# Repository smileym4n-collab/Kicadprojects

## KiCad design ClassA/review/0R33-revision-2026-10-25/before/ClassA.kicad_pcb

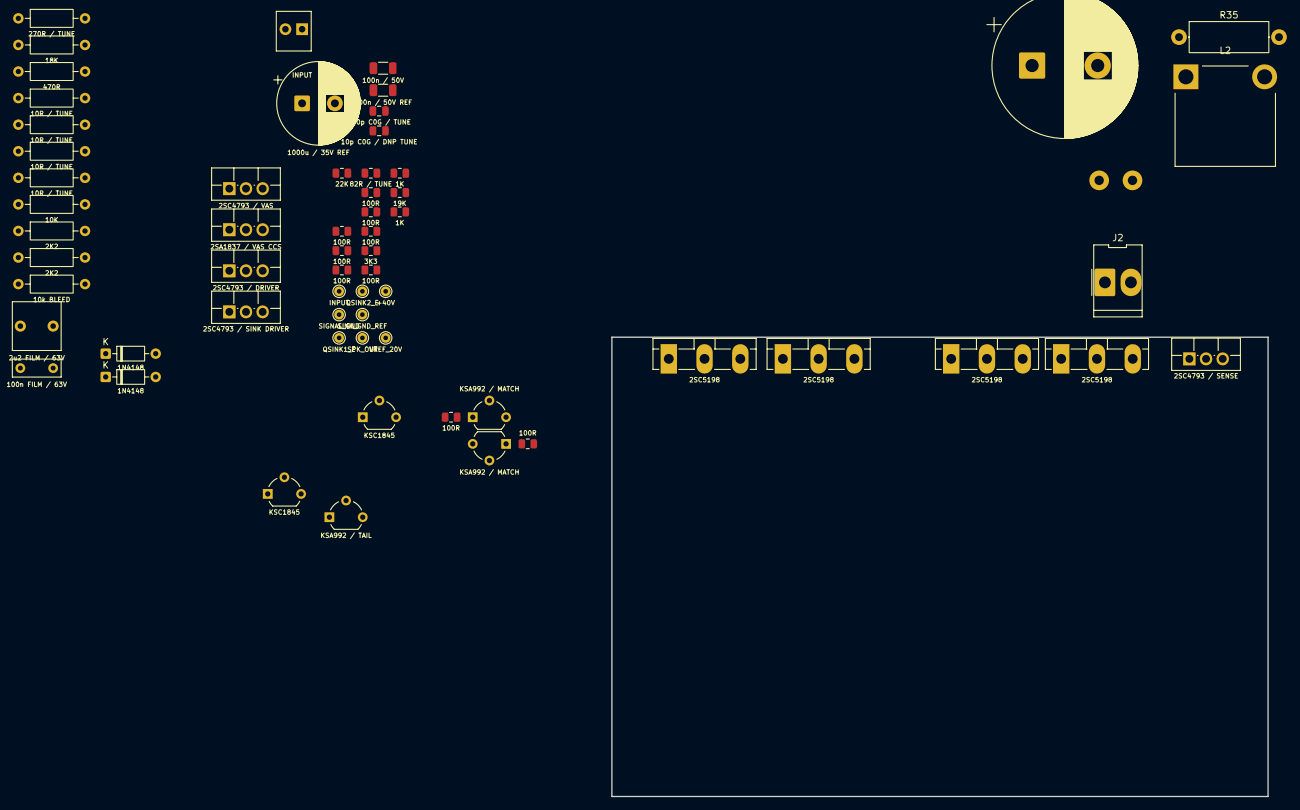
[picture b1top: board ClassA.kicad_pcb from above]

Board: 2 copper layers, 100.0 x 70.0 mm, 63 parts (0 on the bottom side), 35 nets, no tracks yet.

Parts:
C1: 2u2 FILM / 63V; C_Rect_L7.2mm_W7.2mm_P5.00mm
C2: 100p C0G / TUNE; C_0805_2012Metric
C3: 100n FILM / 63V; C_Rect_L7.2mm_W2.5mm_P5.00mm
C5: 10p C0G / DNP TUNE; C_0805_2012Metric
C7: 100n / 50V; C_1206_3216Metric
C8: 1000u / 35V REF; CP_Radial_D12.5mm_P5.00mm
C9: 100n / 50V REF; C_1206_3216Metric
C10: 4700u / 50V; CP_Radial_D22.0mm_P10.00mm_SnapIn
D1, D2: 1N4148; D_DO-35_SOD27_P7.62mm_Horizontal
J1: INPUT; Multicomp_MC34629_1x02_P2.54mm
J2: 40V; Molex_KK-396_5273-02A_1x02_P3.96mm_Vertical
J4: OUT; TE_62409-1
L2: 0.95uH; L_Yamaha_L505_15x15mm_P12mm
Q1, Q2: KSA992 / MATCH; TO-92_Wide
Q3: KSA992 / TAIL; TO-92_Wide
Q4, Q5: KSC1845; TO-92_Wide
Q6: 2SC4793 / VAS; TO-220F-3_Vertical
Q7: 2SA1837 / VAS CCS; TO-220F-3_Vertical
Q8: 2SC4793 / DRIVER; TO-220F-3_Vertical
Q9: 2SC4793 / SINK DRIVER; TO-220F-3_Vertical
Q10: 2SC4793 / SENSE; TO-220F-3_Vertical
QOUT1, QOUT2: 2SC5198; TO-3P-3_Vertical
QSINK1, QSINK2: 2SC5198; TO-3P-3_Vertical
R1: 22K; R_0805_2012Metric
R3, R4, R6, R7, R8, R11, R22, R23, R26: 100R; R_0805_2012Metric
R5: 270R / TUNE; R_Axial_DIN0207_L6.3mm_D2.5mm_P10.16mm_Horizontal
R9: 82R / TUNE; R_0805_2012Metric
R10: 18K; R_Axial_DIN0207_L6.3mm_D2.5mm_P10.16mm_Horizontal
R12: 470R; R_Axial_DIN0207_L6.3mm_D2.5mm_P10.16mm_Horizontal
R13, R14, R17, R18: 10R / TUNE; R_Axial_DIN0207_L6.3mm_D2.5mm_P10.16mm_Horizontal
R24: 10K; R_Axial_DIN0207_L6.3mm_D2.5mm_P10.16mm_Horizontal
R25: 3K3; R_0805_2012Metric
R27, R31: 1K; R_0805_2012Metric
R30: 19K; R_0805_2012Metric
R32, R33: 2K2; R_Axial_DIN0207_L6.3mm_D2.5mm_P10.16mm_Horizontal
R34: 10k BLEED; R_Axial_DIN0207_L6.3mm_D2.5mm_P10.16mm_Horizontal
R35: 10R; R_Axial_DIN0414_L11.9mm_D4.5mm_P15.24mm_Horizontal
TP1: INPUT; TestPoint_THTPad_D1.5mm_Drill0.7mm
TP2: SIGNAL_GND; TestPoint_THTPad_D1.5mm_Drill0.7mm
TP7: QSINK1_E; TestPoint_THTPad_D1.5mm_Drill0.7mm
TP8: QSINK2_E; TestPoint_THTPad_D1.5mm_Drill0.7mm
TP10: SINK_GND_REF; TestPoint_THTPad_D1.5mm_Drill0.7mm
TP12: SPK_OUT; TestPoint_THTPad_D1.5mm_Drill0.7mm
TP13: +40V; TestPoint_THTPad_D1.5mm_Drill0.7mm
TP16: VREF_20V; TestPoint_THTPad_D1.5mm_Drill0.7mm

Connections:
/+40V: C7.1, D1.2 (A), J2.2, Q8.2 (C), QOUT1.2 (C), QOUT2.2 (C), R5.1, R9.1, R24.1, R32.1, TP13.1 (1_1)
/AMP_OUT: C3.1, C5.1, L2.1, Q9.2 (C), QSINK1.2 (C), QSINK2.2 (C), R12.2, R30.1, R35.1
/INPUT: C1.1, J1.1, TP1.1 (1_1)
/IN_PLUS: C1.2, Q1.3 (B), R1.1
/NFB: C5.2, Q2.3 (B), R30.2, R31.1
/PRE_CAP: C10.1, L2.2, R35.2
/P_BIAS: D2.1 (K), Q3.3 (B), Q7.1 (B), R10.1
/SENSE_AVG: R22.1, R23.1, R27.1
/SINK_BASE: Q9.3 (E), R17.1, R18.1
/SINK_CTRL: Q9.1 (B), Q10.2 (C), R24.2
/SPK_OUT: C10.2, J4.1, J4.2 (P1), R34.1, TP12.1 (1_1)
/UPPER_BASE: Q8.3 (E), R12.1, R13.1, R14.1
/VAS_B: C2.1, Q1.2 (C), Q4.2 (C), Q6.1 (B)
/VAS_OUT: C2.2, Q6.2 (C), Q7.2 (C), R11.1
/VREF_20V: C8.1, C9.1, R1.2, R32.2, R33.1, TP16.1 (1_1)
GND: C7.2, C8.2, C9.2, J1.2, J2.1, Q10.3 (E), R6.2, R7.2, R8.2, R10.2, R25.2, R33.2, R34.2, TP2.1 (1_1), TP10.1 (1_1)
unnamed: D1.1 (K), D2.2 (A)
unnamed: Q1.1 (E), R3.2
unnamed: Q2.2 (C), Q5.2 (C)
unnamed: Q2.1 (E), R4.2
unnamed: Q3.2 (C), R3.1, R4.1
unnamed: Q3.1 (E), R5.2
unnamed: Q4.3 (B), Q5.3 (B)
unnamed: Q4.1 (E), R6.1
unnamed: Q5.1 (E), R7.1
unnamed: Q6.3 (E), R8.1
unnamed: Q7.3 (E), R9.2
unnamed: Q8.1 (B), R11.2
unnamed: Q10.1 (B), R26.2, R27.2
unnamed: QOUT1.1 (B), R13.2
unnamed: QOUT2.1 (B), R14.2
unnamed: QSINK1.1 (B), R17.2
unnamed: QSINK1.3 (E), R22.2, TP7.1 (1_1)
unnamed: QSINK2.1 (B), R18.2
unnamed: QSINK2.3 (E), R23.2, TP8.1 (1_1)

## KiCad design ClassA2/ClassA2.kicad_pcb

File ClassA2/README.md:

# ClassA2 — Hiraga-inspired Class-A amplifier (Rev A, schematic for review)

This is one mono channel of a discrete Class-A amplifier: build two boards for stereo. It keeps the basic shape of Jean Hiraga's *Le Monstre*: complementary push-pull from input to output, one complementary-feedback-pair output stage at about 0.7 A, low rails and moderate global feedback. The bias is set by a heatsink-mounted VBE multiplier, and every stage uses transistors from your inventory. Q1/Q2 are 2SC1815-GR, leaving the 2SC2240-GR stock for DarlingtonAmpDual.

**Status:**
- **Schematic:** KiCad ERC 0 errors / 0 warnings, netlist cross-checked against the SPICE deck. Not released for PCB.
- **Simulation:** done, with author-approximate models.
- **Bench tests:** none yet.
- **PCB:** the file is the original empty one, untouched.

| Target | Result (simulation, nominal rails) |
|---|---|
| Output | Class A to 7.5 W / 8 Ω; 12 W at 1 % THD (10.3 W at low mains) |
| Supply | external ±V; 12-0-12 VAC 100 VA gives ±15.6 V loaded (14.1–17.6 V over mains range) |
| Bias | 0.70 A per channel (231 mV across each 0R33), adjustable 0.075–0.94 A, fail-safe trimmer |
| Gain / input impedance | 24.4 dB / ≈ 46 kΩ |
| Response | −0.03 dB at 20 Hz, −0.07 dB at 20 kHz |
| Offset | −15 mV untrimmed; RV2 trims about +17 to −47 mV |
| Stability | 82–95° phase margin, ≥ 23 dB gain margin, open load to 10 µF (with L1) |
| THD (model estimate) | 0.0015 % at 1 W, 0.006 % at 7.5 W, 1 kHz |
| Idle dissipation | 22 W per channel; heatsink ≤ 1.1 K/W per channel |

Files:
- `ClassA2.kicad_sch` and `docs/Schematic.pdf` — the schematic. It is generated by `tools/build_schematic.py`, and **rerunning that script overwrites manual edits.**
- `ClassA2.kicad_sym` / `ClassA2.pretty` — project power-rail symbols and two inventory footprints.
- `BOM.csv` — 71 parts per channel, with stereo quantities, MPNs and inventory status.
- `docs/DESIGN.md` — the Hiraga research, architecture choice, each stage, component rationale, power supply, bias/thermal/SOA calculations, layout intent and open items.
- `docs/SIMULATION.md` — models, method, all results and plots.
- `docs/BENCH_TEST.md` — pre-power checks, bias adjustment procedure and commissioning checklist.
- `simulation/` — ngspice deck (`amp.cir`), models, run scripts (`verify_all.py`, `psu.py`, `pdiss.py`) and results.
- `work/ERC.rpt`, `work/netlist_check.json` — verification evidence. `work/original/` holds the starting project files.

To buy:
- J2: 2 × Molex 09-65-2038.
- 14 Keystone 5000-series test points.
- Enamelled wire for L1.
- R28 (Stackpole RSMF2JT10R0) is already on order.
- 2 × Nichicon UES1H221MHM for C9: the 2 on order go to DarlingtonAmpDual.
- C1: 2 × WIMA MKS2C042201K00KSSD, or two stocked KEMET R82 1 µF in parallel per channel (the stocked WIMAs go to DarlingtonAmpDual).

Points to settle before layout:
- The 2SC2705/2SA1145 pinout needs confirming with a meter.
- The L1 footprint is a placeholder.

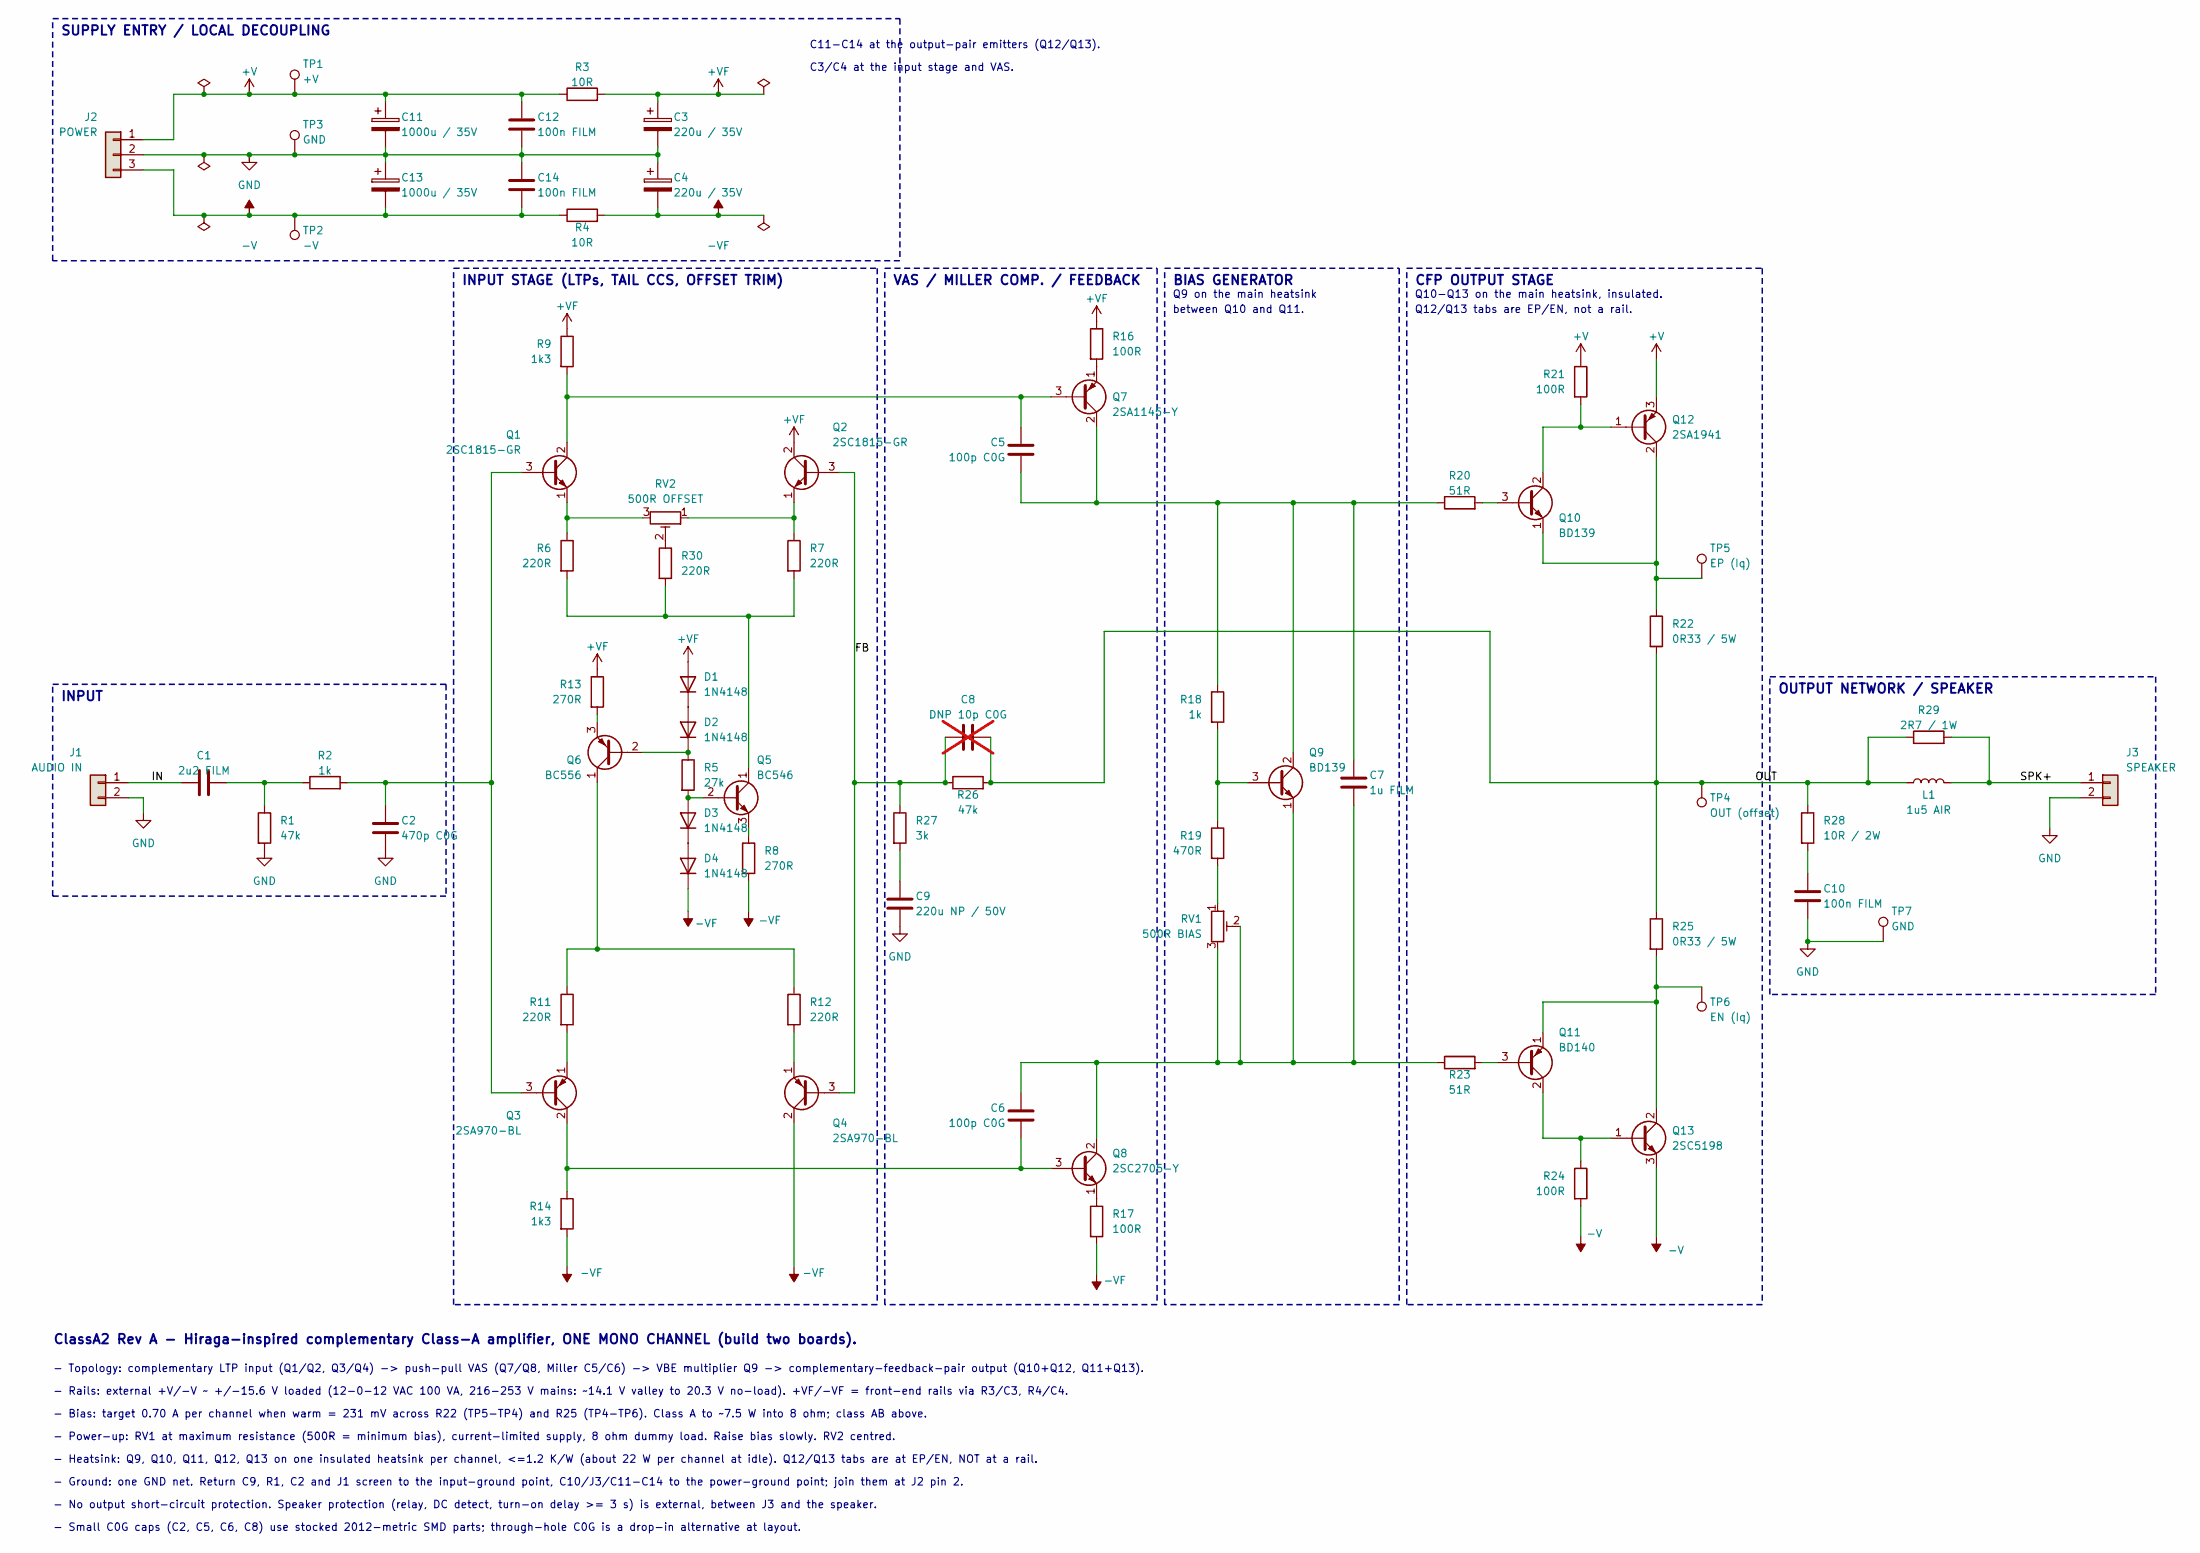
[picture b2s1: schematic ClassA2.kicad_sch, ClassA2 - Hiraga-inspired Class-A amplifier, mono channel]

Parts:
C1: 2u2 FILM; C_Rect_L7.2mm_W7.2mm_P5.00mm_FKS2_FKP2_MKS2_MKP2; Rating 63V PET; MPN MKS2C042201K00KSSD
C2: 470p C0G; C_0805_2012Metric_Pad1.18x1.45mm_HandSolder; Rating 50V C0G 5% 2012 metric; MPN 0805N471J500CT
C3, C4: 220u / 35V; CP_Radial_D8.0mm_P3.50mm; Rating 35V ZLH; MPN 35ZLH220MEFC8X11.5
C5, C6: 100p C0G; C_0805_2012Metric_Pad1.18x1.45mm_HandSolder; Rating 50V C0G 5% 2012 metric; MPN CL21C101JBANNNC
C7: 1u FILM; C_Rect_L7.2mm_W5.5mm_P5.00mm_FKS2_FKP2_MKS2_MKP2; Rating 63V PET; MPN R82DC4100AA60J
C8: DNP 10p C0G; C_0805_2012Metric_Pad1.18x1.45mm_HandSolder; MPN (DNP); not fitted
C9: 220u NP / 50V; C_Radial_D16.0mm_H25.0mm_P7.50mm; Rating 50V bipolar ES series; MPN UES1H221MHM
C10, C12, C14: 100n FILM; C_Rect_L7.2mm_W2.5mm_P5.00mm_FKS2_FKP2_MKS2_MKP2; Rating 63V PET; MPN R82DC3100DQ50J
C11, C13: 1000u / 35V; CP_Radial_D12.5mm_P5.00mm; Rating 35V 105C low-ESR FR; MPN EEU-FR1V102
D1, D2, D3, D4: 1N4148; D_DO-35_SOD27_P7.62mm_Horizontal; MPN 1N4148
J1: AUDIO IN; Multicomp_MC34629_1x02_P2.54mm; MPN MC34629 (+ MC34481 housing)
J2: POWER; Molex_KK-396_A-41791-0003_1x03_P3.96mm_Vertical; MPN 09-65-2038
J3: SPEAKER; Molex_KK-396_A-41791-0002_1x02_P3.96mm_Vertical; MPN 09-65-2028
L1: 1u5 AIR; MPN Self-wound: 17 turns 1.0 mm enamelled C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
Q1: 2SC1815-GR; TO-92_Inline; Rating 50V 150mA 400mW, hFE 200-400, Cob 2pF; MPN 2SC1815-GR
Q2: 2SC1815-GR; TO-92_Inline; Rating 50V 150mA 400mW; MPN 2SC1815-GR
Q3: 2SA970-BL; TO-92_Inline; Rating -120V -100mA 300mW, hFE 350-700; MPN 2SA970-BL
Q4: 2SA970-BL; TO-92_Inline; Rating -120V -100mA 300mW; MPN 2SA970-BL
Q5: BC546; TO-92_Inline; Rating 65V 100mA; MPN BC546B (ST BC546 stocked)
Q6: BC556; TO-92_Inline; Rating -65V -100mA; MPN BC556B
Q7: 2SA1145-Y; TO-92L_Inline; Rating -150V -50mA 0.8W, Cob 2.5pF; MPN 2SA1145-Y
Q8: 2SC2705-Y; TO-92L_Inline; Rating 150V 50mA 0.8W, Cob 1.8pF; MPN 2SC2705-Y
Q9, Q10: BD139; TO-126-3_Vertical; Rating 80V 1.5A 12.5W; MPN BD139
Q11: BD140; TO-126-3_Vertical; Rating -80V -1.5A 12.5W; MPN BD140
Q12: 2SA1941; TO-3P-3_Vertical; Rating -140V -10A 100W(Tc25), Rth(j-c) 1.25K/W; MPN 2SA1941-O (R or O rank)
Q13: 2SC5198; TO-3P-3_Vertical; Rating 140V 10A 100W(Tc25), Rth(j-c) 1.25K/W; MPN 2SC5198-O (R or O rank)
R1, R26: 47k; R_Axial_DIN0207_L6.3mm_D2.5mm_P10.16mm_Horizontal; Rating 0.6W 1% metal film; MPN LR1F47K
R2, R18: 1k; R_Axial_DIN0207_L6.3mm_D2.5mm_P10.16mm_Horizontal; Rating 0.6W 1% metal film; MPN LR1F1K
R3, R4: 10R; R_Axial_DIN0207_L6.3mm_D2.5mm_P10.16mm_Horizontal; Rating 0.6W 1% metal film; MPN LR1F10R
R5: 27k; R_Axial_DIN0207_L6.3mm_D2.5mm_P10.16mm_Horizontal; Rating 0.6W 1% metal film; MPN LR1F27K
R6, R7, R11, R12, R30: 220R; R_Axial_DIN0207_L6.3mm_D2.5mm_P10.16mm_Horizontal; Rating 0.6W 1% metal film; MPN LR1F220R
R8, R13: 270R; R_Axial_DIN0207_L6.3mm_D2.5mm_P10.16mm_Horizontal; Rating 0.6W 1% metal film; MPN LR1F270R
R9, R14: 1k3; R_Axial_DIN0207_L6.3mm_D2.5mm_P10.16mm_Horizontal; Rating 0.5W 1% metal film; MPN MF50 1K3
R16, R17, R21, R24: 100R; R_Axial_DIN0207_L6.3mm_D2.5mm_P10.16mm_Horizontal; Rating 0.6W 1% metal film; MPN LR1F100R
R19: 470R; R_Axial_DIN0207_L6.3mm_D2.5mm_P10.16mm_Horizontal; Rating 0.6W 1% metal film; MPN LR1F470R
R20, R23: 51R; R_Axial_DIN0207_L6.3mm_D2.5mm_P10.16mm_Horizontal; Rating 0.6W 1% metal film; MPN LR1F51R
R22, R25: 0R33 / 5W; Yageo_SQP500_L22.0mm_W9.5mm_P30.48mm; Rating 5W 5% cement; MPN SQP500JB-0R33
R27: 3k; R_Axial_DIN0207_L6.3mm_D2.5mm_P10.16mm_Horizontal; Rating 0.6W 1% metal film; MPN LR1F3K0
R28: 10R / 2W; R_Axial_DIN0414_L11.9mm_D4.5mm_P15.24mm_Horizontal; Rating 2W 5% metal oxide (non-inductive); MPN RSMF2JT10R0
R29: 2R7 / 1W; R_Axial_DIN0207_L6.3mm_D2.5mm_P10.16mm_Horizontal; Rating 1W 5% metal film; MPN RR01J2R7TB
RV1: 500R BIAS; Potentiometer_Bourns_3296W_Vertical; Rating multi-turn cermet; MPN 3296W-1-501LF (stocked generic 500R mul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
RV2: 500R OFFSET; Potentiometer_Bourns_3296W_Vertical; Rating multi-turn cermet; MPN 3296W-1-501LF (stocked generic 500R mul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
TP1: +V; TestPoint_Keystone_5000-5004_Miniature; MPN 5000
TP2: -V; TestPoint_Keystone_5000-5004_Miniature; MPN 5004
TP3, TP7: GND; TestPoint_Keystone_5000-5004_Miniature; MPN 5001
TP4: OUT (offset); TestPoint_Keystone_5000-5004_Miniature; MPN 5002
TP5: EP (Iq); TestPoint_Keystone_5000-5004_Miniature; MPN 5003
TP6: EN (Iq); TestPoint_Keystone_5000-5004_Miniature; MPN 5003

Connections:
+V: C11.1, C12.1, J2.1, Q12.3 (E), R3.1, R21.1, TP1.1 (1_1)
+VF: C3.1, D1.2 (A), Q2.2 (C), R3.2, R9.1, R13.1, R16.1
-V: C13.2, C14.2, J2.3, Q13.3 (E), R4.1, R24.2, TP2.1 (1_1)
-VF: C4.2, D4.1 (K), Q4.2 (C), R4.2, R8.2, R14.2, R17.2
/FB: C8.1, Q2.3 (B), Q4.3 (B), R26.1, R27.1
/IN: C1.1, J1.1
/OUT: C8.2, L1.1, R22.2, R25.1, R26.2, R28.1, R29.1, TP4.1 (1_1)
/SPK+: J3.1, L1.2, R29.2
GND: C2.2, C3.2, C4.1, C9.2, C10.2, C11.2, C12.2, C13.1, C14.1, J1.2, J2.2, J3.2, R1.2, TP3.1 (1_1), TP7.1 (1_1)
unnamed: C1.2, R1.1, R2.1
unnamed: C9.1, R27.2
unnamed: C10.1, R28.2
unnamed: D1.1 (K), D2.2 (A)
unnamed: D2.1 (K), Q6.2 (B), R5.1
unnamed: D3.2 (A), Q5.2 (B), R5.2
unnamed: D3.1 (K), D4.2 (A)
unnamed: C2.1, Q1.3 (B), Q3.3 (B), R2.2
unnamed: C5.1, Q1.2 (C), Q7.3 (B), R9.2
unnamed: Q1.1 (E), R6.1, RV2.3
unnamed: Q2.1 (E), R7.1, RV2.1
unnamed: C6.2, Q3.2 (C), Q8.3 (B), R14.1
unnamed: Q3.1 (E), R11.2
unnamed: Q4.1 (E), R12.2
unnamed: Q5.1 (C), R6.2, R7.2, R30.2
unnamed: Q5.3 (E), R8.1
unnamed: Q6.1 (C), R11.1, R12.1
unnamed: Q6.3 (E), R13.2
unnamed: C5.2, C7.1, Q7.2 (C), Q9.2 (C), R18.1, R20.1
unnamed: Q7.1 (E), R16.2
unnamed: C6.1, C7.2, Q8.2 (C), Q9.1 (E), R23.1, RV1.2, RV1.3
unnamed: Q8.1 (E), R17.1
unnamed: Q9.3 (B), R18.2, R19.1
unnamed: Q10.3 (B), R20.2
unnamed: Q10.2 (C), Q12.1 (B), R21.2
unnamed: Q10.1 (E), Q12.2 (C), R22.1, TP5.1 (1_1)
unnamed: Q11.3 (B), R23.2
unnamed: Q11.2 (C), Q13.1 (B), R24.1
unnamed: Q11.1 (E), Q13.2 (C), R25.2, TP6.1 (1_1)
unnamed: R19.2, RV1.1
unnamed: R30.1, RV2.2

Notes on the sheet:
SUPPLY ENTRY / LOCAL DECOUPLING
- Small C0G caps (C2, C5, C6, C8) use stocked 2012-metric SMD parts; through-hole C0G is a drop-in alternative at layout.
- Power-up: RV1 at maximum resistance (500R = minimum bias), current-limited supply, 8 ohm dummy load. Raise bias slowly. RV2 centred.
between Q10 and Q11.
OUTPUT NETWORK / SPEAKER
- Rails: external +V/-V ~ +/-15.6 V loaded (12-0-12 VAC 100 VA, 216-253 V mains: ~14.1 V valley to 20.3 V no-load). +VF/-VF = front-end rails via R3/C3, R4/C4.
VAS / MILLER COMP. / FEEDBACK
Q10-Q13 on the main heatsink, insulated.
- Topology: complementary LTP input (Q1/Q2, Q3/Q4) -> push-pull VAS (Q7/Q8, Miller C5/C6) -> VBE multiplier Q9 -> complementary-feedback-pair output (Q10+Q12, Q11+Q13).
C3/C4 at the input stage and VAS.
ClassA2 Rev A - Hiraga-inspired complementary Class-A amplifier, ONE MONO CHANNEL (build two boards).
BIAS GENERATOR
INPUT
Q12/Q13 tabs are EP/EN, not a rail.
- Ground: one GND net. Return C9, R1, C2 and J1 screen to the input-ground point, C10/J3/C11-C14 to the power-ground point; join them at J2 pin 2.
- No output short-circuit protection. Speaker protection (relay, DC detect, turn-on delay >= 3 s) is external, between J3 and the speaker.
C11-C14 at the output-pair emitters (Q12/Q13).
- Heatsink: Q9, Q10, Q11, Q12, Q13 on one insulated heatsink per channel, <=1.2 K/W (about 22 W per channel at idle). Q12/Q13 tabs are at EP/EN, NOT at a rail.
- Bias: target 0.70 A per channel when warm = 231 mV across R22 (TP5-TP4) and R25 (TP4-TP6). Class A to ~7.5 W into 8 ohm; class AB above.
INPUT STAGE (LTPs, TAIL CCS, OFFSET TRIM)
CFP OUTPUT STAGE
Q9 on the main heatsink

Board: 2 copper layers, 72 parts (0 on the bottom side), 40 nets, no tracks yet.

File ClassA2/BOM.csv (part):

References,Qty_per_channel,Qty_stereo,Value,Description,Manufacturer,MPN,Rating,Package,KiCad_footprint,Inventory,DNP,Notes,Datasheet
C1,1,2,2u2 FILM,Film capacitor,WIMA,MKS2C042201K00KSSD,63V PET,THT,Capacitor_THT:C_Rect_L7.2mm_W7.2mm_P5.00mm_FKS2_FKP2_MKS2_MKP2,BUY 2 (stocked inv 417 reserved for DarlingtonAmpDual),,Input DC block. With R1 = 47k: 1.54 Hz. Stock alternative: 2 x KEMET R82DC4100AA60J 1u in parallel. PP film is an optional like-for-like upgrade.,
C2,1,2,470p C0G,C0G capacitor,Multicomp Pro,0805N471J500CT,50V C0G 5% 2012 metric,2012 metric SMD,Capacitor_SMD:C_0805_2012Metric_Pad1.18x1.45mm_HandSolder,IN STOCK (inv 337),,RF filter to GND; return to input ground.,
C3 C4,2,4,220u / 35V,Electrolytic,Rubycon,35ZLH220MEFC8X11.5,35V ZLH,THT,Capacitor_THT:CP_Radial_D8.0mm_P3.50mm,IN STOCK (inv 366),,Front-end +VF decoupling; at the input-stage/VAS area.,
C5 C6,2,4,100p C0G,C0G capacitor,Samsung,CL21C101JBANNNC,50V C0G 5% 2012 metric,2012 metric SMD,Capacitor_SMD:C_0805_2012Metric_Pad1.18x1.45mm_HandSolder,IN STOCK (inv 197),,"Miller compensation, VAS collector to base. Do not reduce without a loop re-test.",
C7,1,2,1u FILM,Film capacitor,KEMET,R82DC4100AA60J,63V PET,THT,Capacitor_THT:C_Rect_L7.2mm_W5.5mm_P5.00mm_FKS2_FKP2_MKS2_MKP2,IN STOCK (inv 132),,Ties both driver bases together at AF/HF.,
C8,0,0,DNP 10p C0G,C0G capacitor,,(DNP),,2012 metric SMD,Capacitor_SMD:C_0805_2012Metric_Pad1.18x1.45mm_HandSolder,DNP,DNP,FB LEAD DNP: optional phase-lead across R26 if bench square waves show ringing; not needed in simulation.,
C9,1,2,220u NP / 50V,Bipolar electrolytic,Nichicon,UES1H221MHM,50V bipolar ES series,THT,Capacitor_THT:C_Radial_D16.0mm_H25.0mm_P7.50mm,BUY 2 (inv 501 on-order pair reserved for DarlingtonAmpDual),,Feedback DC block: DC gain = 1. 3k x 220u = 0.24 Hz. Bipolar; ~15 mV across it.,
C10 C12 C14,3,6,100n FILM,Film capacitor,KEMET,R82DC3100DQ50J,63V PET,THT,Capacitor_THT:C_Rect_L7.2mm_W2.5mm_P5.00mm_FKS2_FKP2_MKS2_MKP2,IN STOCK (inv 406),,Zobel capacitor; GND return to output/speaker ground.,
C11 C13,2,4,1000u / 35V,Electrolytic,Panasonic,EEU-FR1V102,35V 105C low-ESR FR,THT,Capacitor_THT:CP_Radial_D12.5mm_P5.00mm,"IN STOCK (inv 338, 8 pcs)",,Place at Q12 emitter / +V entry. Local reservoir only; main PSU caps are off-board.,
D1 D2 D3 D4,4,8,1N4148,Signal diode,onsemi,1N4148,,THT,Diode_THT:D_DO-35_SOD27_P7.62mm_Horizontal,IN STOCK (inv 138),,Tail reference.,https://www.onsemi.com/pdf/datasheet/1n914-d.pdf
J1,1,2,AUDIO IN,"2.54 mm 2-way header to chassis RCA, screened lead",Multicomp Pro,MC34629 (+ MC34481 housing),,THT,ClassA2:Multicomp_MC34629_1x02_P2.54mm,IN STOCK (inv 126 / 128),,"1 = signal, 2 = signal ground (screen).",
J2,1,2,POWER,"KK-396 3-way header, 7 A per contact",Molex,09-65-2038,,THT,Connector_Molex:Molex_KK-396_A-41791-0003_1x03_P3.96mm_Vertical,BUY (2 for stereo),,"1 = +V, 2 = GND, 3 = -V. External symmetrical DC from the shared PSU.",
J3,1,2,SPEAKER,"KK-396 2-way header, 7 A per contact",Molex,09-65-2028,,THT,Connector_Molex:Molex_KK-396_A-41791-0002_1x02_P3.96mm_Vertical,"IN STOCK (inv 722, 16 pcs)",,"1 = SPK+ (amplifier output), 2 = speaker return to GND. External speaker protection goes in series here.",
L1,1,2,1u5 AIR,Air-core inductor,,"Self-wound: 17 turns 1.0 mm enamelled Cu, 10 mm former (~1.5 uH)",,THT,Inductor_THT:L_Axial_L14.5mm_D5.8mm_P20.32mm_Horizontal_Fastron_HBCC,MAKE,,Output isolation coil; required for capacitive-load stability (sim: 1.9 MHz oscillation into 100 nF without it). Footprint is a placeholder: match the coil at layout.,
Q1 Q2,2,4,2SC1815-GR,,Toshiba,2SC1815-GR,"50V 150mA 400mW, hFE 200-400, Cob 2pF",THT,Package_TO_SOT_THT:TO-92_Inline,"IN STOCK (inv 386, 6 pcs; 4 needed)",,"Pins 1E 2C 3B (2-5F1B, same as 2SC2240). Replaces 2SC2240-GR (stock kept for DarlingtonAmpDual). Match Q1/Q2 VBE and hFE; thermally couple.",https://akizukidenshi.com/goodsaffix/2sc1815-gr.pdf
Q3 Q4,2,4,2SA970-BL,,Toshiba,2SA970-BL,"-120V -100mA 300mW, hFE 350-700",THT,Package_TO_SOT_THT:TO-92_Inline,"IN STOCK (inv 614, 17 pcs; 4 needed)",,Pins 1E 2C 3B (2-5F1B). Match Q3/Q4.,https://www.micros.com.pl/mediaserver/info-t2sa9702sc2240.pdf
Q5,1,2,BC546,,STMicroelectronics,BC546B (ST BC546 stocked),65V 100mA,THT,Package_TO_SOT_THT:TO-92_Inline,IN STOCK (inv 254),,NPN tail CCS ~1.95 mA. Pins 1C 2B 3E - check the fitted brand.,http://www.farnell.com/datasheets/2277528.pdf
Q6,1,2,BC556,,onsemi,BC556B,-65V -100mA,THT,Package_TO_SOT_THT:TO-92_Inline,IN STOCK (inv 462),,PNP tail CCS ~2.0 mA. Pins 1C 2B 3E (onsemi).,https://www.onsemi.com/pdf/datasheet/bc556bta-d.pdf
Q7,1,2,2SA1145-Y,,Toshiba,2SA1145-Y,"-150V -50mA 0.8W, Cob 2.5pF",THT,Package_TO_SOT_THT:TO-92L_Inline,"IN STOCK (inv 612, 12 pcs)",,"PNP VAS ~5.5 mA. Pins 1E 2C 3B (TO-92MOD 2-5J1A, second-source sheet): CONFIRM with a meter before fitting.",https://www.ges.cz/2SC2705-2SA1145-Toshiba-par-pro-NF-vykono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
Q8,1,2,2SC2705-Y,,Toshiba,2SC2705-Y,"150V 50mA 0.8W, Cob 1.8pF",THT,Package_TO_SOT_THT:TO-92L_Inline,"IN STOCK (inv 611, 12 pcs)",,NPN VAS ~5.5 mA. Pins 1E 2C 3B (TO-92MOD): CONFIRM with a meter before fitting.,https://www.ges.cz/2SC2705-2SA1145-Toshiba-par-pro-NF-vykono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
Q9 Q10,2,4,BD139,,STMicroelectronics,BD139,80V 1.5A 12.5W,THT,Package_TO_SOT_THT:TO-126-3_Vertical,"IN STOCK (inv 148, 13 pcs)",,VBE multiplier / thermal sensor. Mount on main heatsink between Q10 and Q11 (insulated). Pins 1E 2C 3B.,https://www.st.com/resource/en/datasheet/bd135.pdf
Q11,1,2,BD140,,STMicroelectronics,BD140,-80V -1.5A 12.5W,THT,Package_TO_SOT_THT:TO-126-3_Vertical,IN STOCK (inv 149),,CFP driver. Mount on main heatsink (insulated) next to Q9. Pins 1E 2C 3B.,https://www.st.com/resource/en/datasheet/bd135.pdf
Q12,1,2,2SA1941,,Toshiba,2SA1941-O (R or O rank),"-140V -10A 100W(Tc25), Rth(j-c) 1.25K/W",THT,Package_TO_SOT_THT:TO-3P-3_Vertical,"IN STOCK (inv 147, 19 pcs)",,Upper output. Emitter to +V; collector/tab = EP node. Insulate from heatsink. Pins 1B 2C 3E.,https://toshiba.semicon-storage.com/info/docget.jsp?did=2042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
Q13,1,2,2SC5198,,Toshiba,2SC5198-O (R or O rank),"140V 10A 100W(Tc25), Rth(j-c) 1.25K/W",THT,Package_TO_SOT_THT:TO-3P-3_Vertical,"IN STOCK (inv 141, 20 pcs)",,Lower output. Emitter to -V; collector/tab = EN node. Insulate from heatsink. Pins 1B 2C 3E.,https://toshiba.semicon-storage.com/info/docget.jsp?did=2066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
R1 R26,2,4,47k,Resistor,TE Connectivity,LR1F47K,0.6W 1% metal film,THT,Resistor_THT:R_Axial_DIN0207_L6.3mm_D2.5mm_P10.16mm_Horizontal,IN STOCK (inv 277),,Input resistance / DC reference. Equal to R26 to cancel base-current offset.,
R2 R18,2,4,1k,Resistor,TE Connectivity,LR1F1K,0.6W 1% metal film,THT,Resistor_THT:R_Axial_DIN0207_L6.3mm_D2.5mm_P10.16mm_Horizontal,IN STOCK (inv 285),,Input stopper; with C2 forms a 339 kHz RF filter.,
R3 R4,2,4,10R,Resistor,TE Connectivity,LR1F10R,0.6W 1% metal film,THT,Resistor_THT:R_Axial_DIN0207_L6.3mm_D2.5mm_P10.16mm_Horizontal,IN STOCK (inv 283),,"Front-end supply filter, ~10 mA.",
R5,1,2,27k,Resistor,TE Connectivity,LR1F27K,0.6W 1% metal film,THT,Resistor_THT:R_Axial_DIN0207_L6.3mm_D2.5mm_P10.16mm_Horizontal,IN STOCK (inv 784),,Shared feed for both tail references (~1.05 mA).,
R6 R7 R11 R12 R30,5,10,220R,Resistor,TE Connectivity,LR1F220R,0.6W 1% metal film,THT,Resistor_THT:R_Axial_DIN0207_L6.3mm_D2.5mm_P10.16mm_Horizontal,IN STOCK (inv 152),,Emitter degeneration.,
R8 R13,2,4,270R,Resistor,TE Connectivity,LR1F270R,0.6W 1% metal film,THT,Resistor_THT:R_Axial_DIN0207_L6.3mm_D2.5mm_P10.16mm_Horizontal,IN STOCK (inv 92),,NPN tail current = (2 x Vf - Vbe)/270R.,
R9 R14,2,4,1k3,Resistor,Multicomp Pro,MF50 1K3,0.5W 1% metal film,THT,Resistor_THT:R_Axial_DIN0207_L6.3mm_D2.5mm_P10.16mm_Horizontal,"IN STOCK (inv 763, 9 pcs; 4 needed)",,Q1 load; sets VAS current with R16 (~5.5 mA).,
R16 R17 R21 R24,4,8,100R,Resistor,TE Connectivity,LR1F100R,0.6W 1% metal film,THT,Resistor_THT:R_Axial_DIN0207_L6.3mm_D2.5mm_P10.16mm_Horizontal,IN STOCK (inv 150),,VAS emitter degeneration.,
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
